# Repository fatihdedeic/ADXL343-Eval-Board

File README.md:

# ADXL343-Eval-Board
Small footprint I2C protocol evaluation board designed for ADXL343 series accelerometers.

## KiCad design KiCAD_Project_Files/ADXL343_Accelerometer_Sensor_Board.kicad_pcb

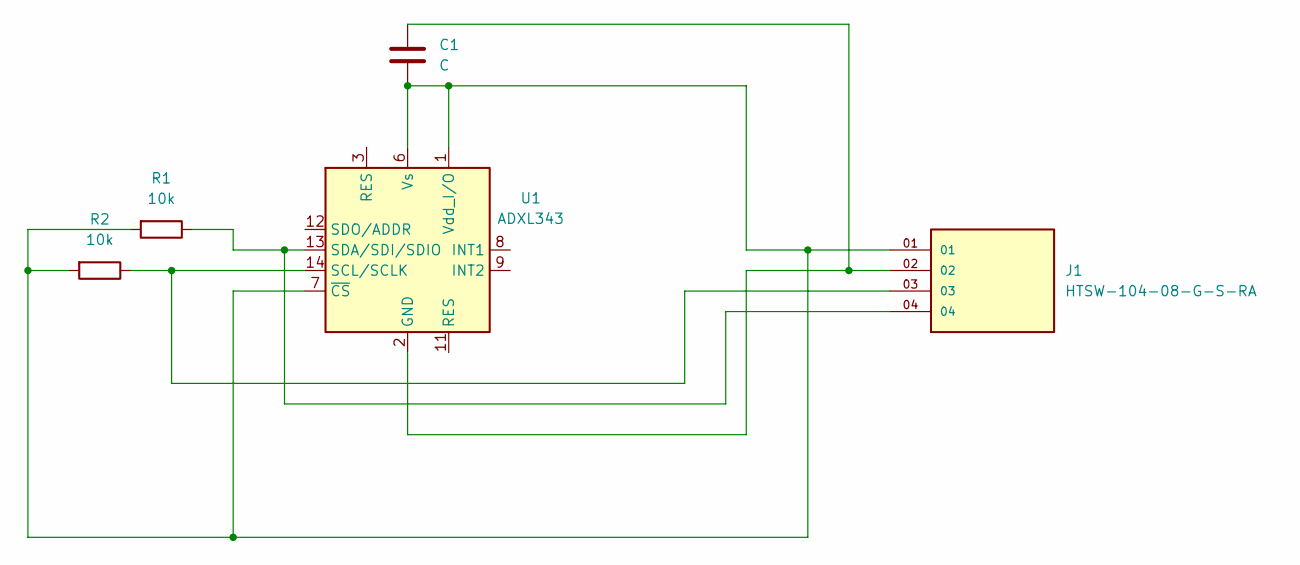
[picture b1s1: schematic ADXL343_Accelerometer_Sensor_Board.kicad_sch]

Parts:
C1: C; C_0201_0603Metric_Pad0.64x0.40mm_HandSolder
J1: HTSW-104-08-G-S-RA; SAMTEC_HTSW-104-08-G-S-RA; PARTREV R
R1, R2: 10k; R_0201_0603Metric_Pad0.64x0.40mm_HandSolder
U1: ADXL343; LGA-14_3x5mm_P0.8mm_LayoutBorder1x6y

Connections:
unnamed: C1.1, J1.02, U1.2 (GND), U1.4 (GND), U1.5 (GND)
unnamed: J1.03, R2.1, U1.14 (SCL/SCLK)
unnamed: J1.04, R1.1, U1.13 (SDA/SDI/SDIO)
unnamed: C1.2, J1.01, R1.2, R2.2, U1.1 (Vdd_I/O), U1.6 (Vs), U1.7 (~CS)

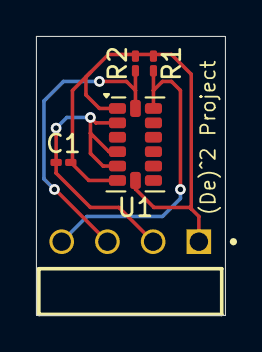
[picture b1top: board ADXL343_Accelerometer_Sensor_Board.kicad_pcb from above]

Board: 2 copper layers, 10.5 x 15.5 mm, 5 parts (0 on the bottom side), 4 nets.

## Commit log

2025-03-09 Delete ADXL343_Footprints.pdf
    Deleted file, going to add in later with rest of files for folder management.
2025-03-09 Added 3D Renders folder
    Added 3D Renders folder
2025-03-09 Create Placeholder_2
    Created Design Documents folder
2025-03-09 Created KiCAD Project Files folder
2025-03-09 Created ADXL343_Accelerometer_Sensor_Board-backups folder
2025-03-09 Update README.md
    Tried to add image to readme file
